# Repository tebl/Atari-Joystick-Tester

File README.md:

# Atari Joystick Tester

Lately I've been going through my rather limited amount, but still designated a "sizable pile", of vintage joysticks. Maybe this was to be the year I got around to fixing them - given that we're constantly fast coming up on december, the time to get moving is definitively now. Did not want to subject one of my computers to all that plugging and unplugging while fiddling with wires and resoldering contacts, so the next step of procrastination was designing a simple joystick tester.

Joystick testers are certainly nothing new so based my design on an already existing one, specifically [http://www.mks.purespace.de/technical/c64tester.htm](http://www.mks.purespace.de/technical/c64tester.htm). So, if like me you feel that prototyping boards and the like are too unreliable and finicky to use in practice you can order a set of my PCB to make a more permanent version of it - if you like and prefer prototyping, then there's the page to start with.

# Schematic
The supplied KiCad files should be sufficient as both a schematic and as a  starting point for ordering PCBs (basically you could just zip the contents of the export folder and upload that on a fabrication site), the schematic is also available in [PDF-format](https://github.com/tebl/Atari-Joystick-Tester/raw/master/export/Atari%20Joystick%20Tester.pdf) and this is what you'll need to print and work your way through this things don't work as expected after assembly.

# BOM
Most parts should be easy to easily get from your favourite local electronic component shop, personally I live around a couple of hours away from the closest one (by plane) so mostly I just use whatever is available via ebay, AliExpress or similar site. Most components coming out of China are good enough for hobby projects such as this, and in quantities usually large enough to build ten of them for less than a somewhat fancy cup of coffee (contents, not counting the actual mug).

Resistor values are highly dependent on the type of LEDs used on the card, usually you'd need to check their datasheets for information on their forward voltage drops and then using that to calculate the proper resistor values to use. Or, just wing it by using 220 for the old style RED/GREEN/YELLOW types, 330 to be safe and 470 for those super-bright modern blue LEDs (you want an indication if it's working, not burn it into your retinas).

| Reference               | Item                                   | Count |
| ----------------------- | -------------------------------------- | ----- |
| PCB                     | Fabricate using Gerber files ([order here](https://www.pcbway.com/project/shareproject/Atari_Joystick_Tester.html?inviteid=88707))  |     1 |
| J1                      | DB9 male connector (2 rows), PCB mount |     1 |
| J4                      | 3 pin DC barrel connector              |     1 |
| SW1,SW2                 | 3pin SPDT slide-switch                 |     2 |
| R1-R7                   | 220-470 ohm resistor (dependent on LED)|     7 | 
| D1-R7                   | 5mm LED, assorted colors as desired    |     7 | 

Please use the order link above when signing up to help me support this project, I'll get a small discount on future orders and hopefully that means I can afford to keep developing new and exciting modules in the future. By using the URL you won't have to deal with the rather daunting order forms for PCB fabrication, but if you want to go that route they'll probably want a zipped-up copy of the files in the export-directory!

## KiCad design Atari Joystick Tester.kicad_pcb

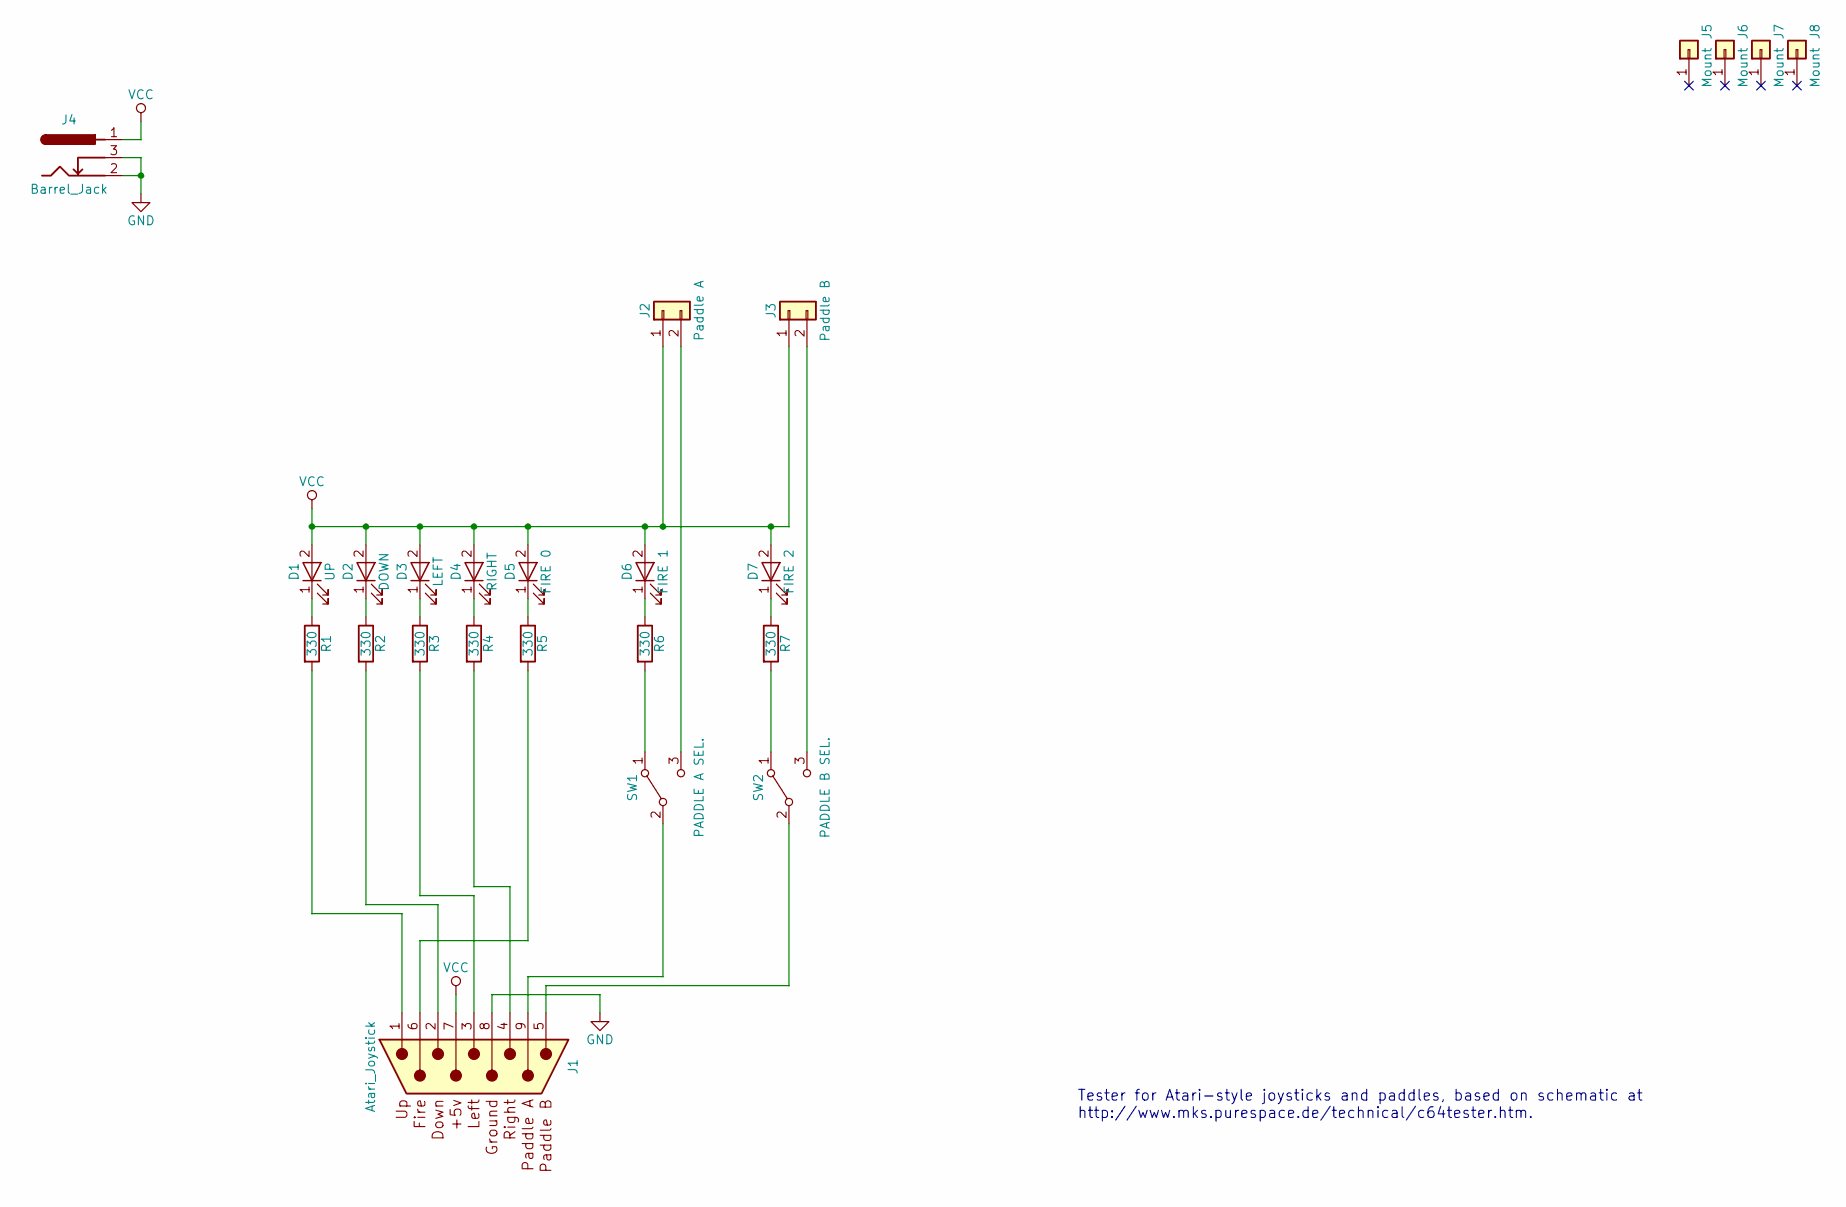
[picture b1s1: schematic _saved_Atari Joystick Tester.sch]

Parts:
D1: UP; LED_D5.0mm
D2: DOWN; LED_D5.0mm
D3: LEFT; LED_D5.0mm
D4: RIGHT; LED_D5.0mm
D5: FIRE 0; LED_D5.0mm
D6: FIRE 1; LED_D5.0mm
D7: FIRE 2; LED_D5.0mm
J1: Atari_Joystick; DSUB-9_Male_Vertical_Pitch2.77x2.84mm
J2: Paddle A; TerminalBlock_bornier-2_P5.08mm
J3: Paddle B; TerminalBlock_bornier-2_P5.08mm
J4: Barrel_Jack; BARREL_JACK
J5, J6, J7, J8: Mount; 1pin
R1, R2, R3, R4, R5, R6, R7: 330; R_Axial_DIN0207_L6.3mm_D2.5mm_P10.16mm_Horizontal
SW1: PADDLE A SEL.; Pin_Header_Straight_1x03_Pitch2.54mm
SW2: PADDLE B SEL.; Pin_Header_Straight_1x03_Pitch2.54mm

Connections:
GND: J1.8, J4.2, J4.3
unnamed: D1.1 (K), R1.1
unnamed: D2.1 (K), R2.1
unnamed: D3.1 (K), R3.1
unnamed: D4.1 (K), R4.1
unnamed: D5.1 (K), R5.1
unnamed: D6.1 (K), R6.1
unnamed: D7.1 (K), R7.1
unnamed: J1.1, R1.2
unnamed: J1.2, R2.2
unnamed: J1.3, R3.2
unnamed: J1.4, R4.2
unnamed: J1.5, SW2.2 (B)
unnamed: J1.6, R5.2
unnamed: J1.9, SW1.2 (B)
unnamed: J2.2, SW1.3 (C)
unnamed: J3.2, SW2.3 (C)
unnamed: R6.2, SW1.1 (A)
unnamed: R7.2, SW2.1 (A)
VCC: D1.2 (A), D2.2 (A), D3.2 (A), D4.2 (A), D5.2 (A), D6.2 (A), D7.2 (A), J1.7, J2.1, J3.1, J4.1

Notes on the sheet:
Tester for Atari-style joysticks and paddles, based on schematic at http://www.mks.purespace.de/technical/c64tester.htm.

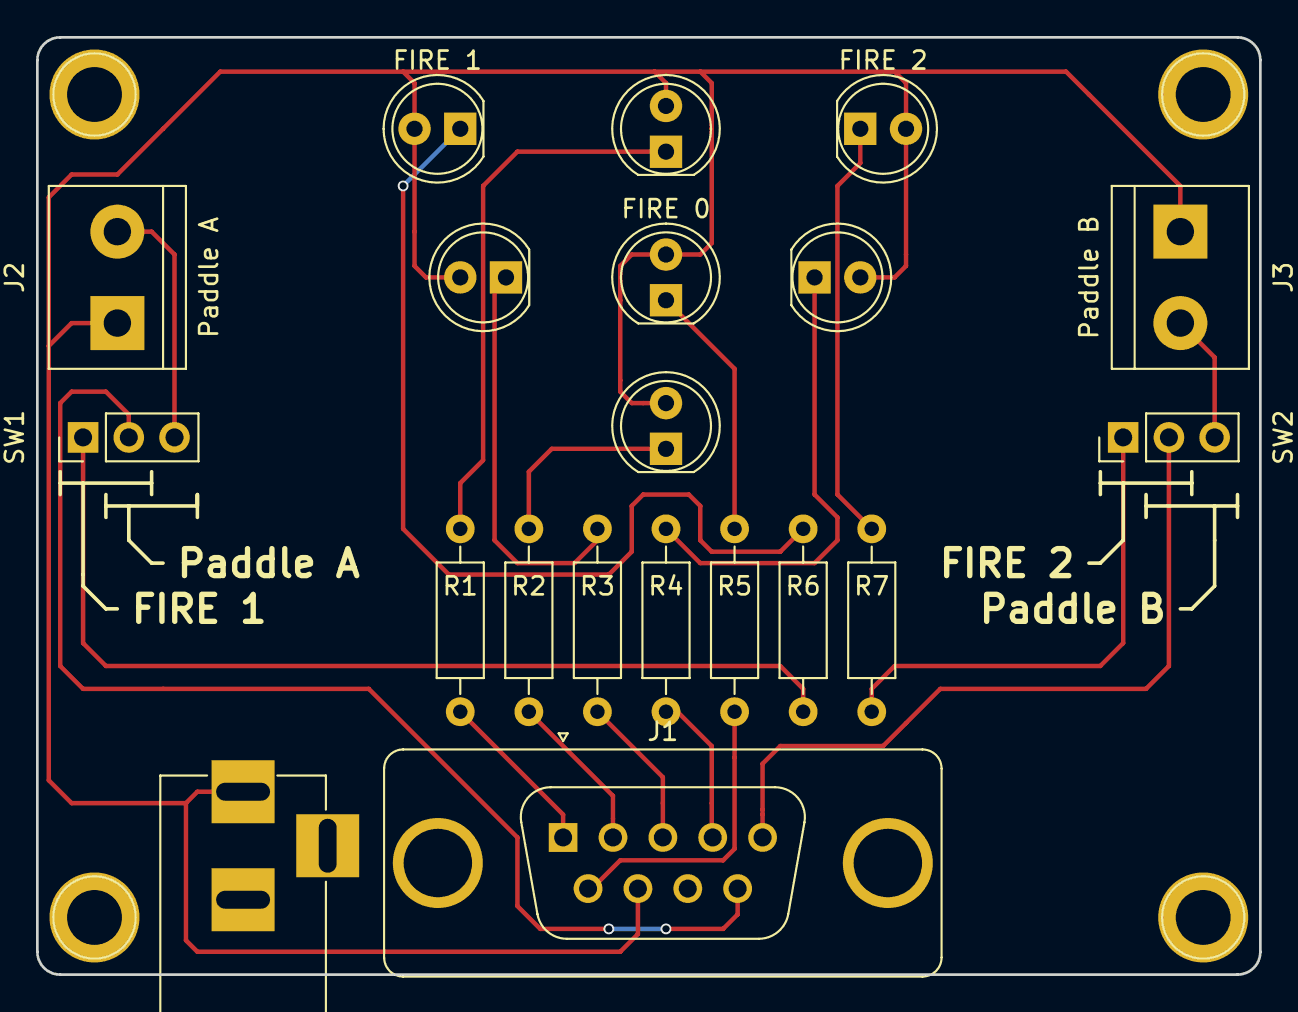
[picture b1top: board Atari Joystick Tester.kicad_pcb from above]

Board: 2 copper layers, 67.9 x 52.1 mm, 24 parts (0 on the bottom side), 20 nets.

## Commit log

2018-11-06 Added schematic
2018-11-06 Basic layout without wires
2018-11-06 Added wires and exported gerber files.
2018-11-08 Reoriented components.
2018-11-28 Added schematic and images
2018-11-28 Added README
